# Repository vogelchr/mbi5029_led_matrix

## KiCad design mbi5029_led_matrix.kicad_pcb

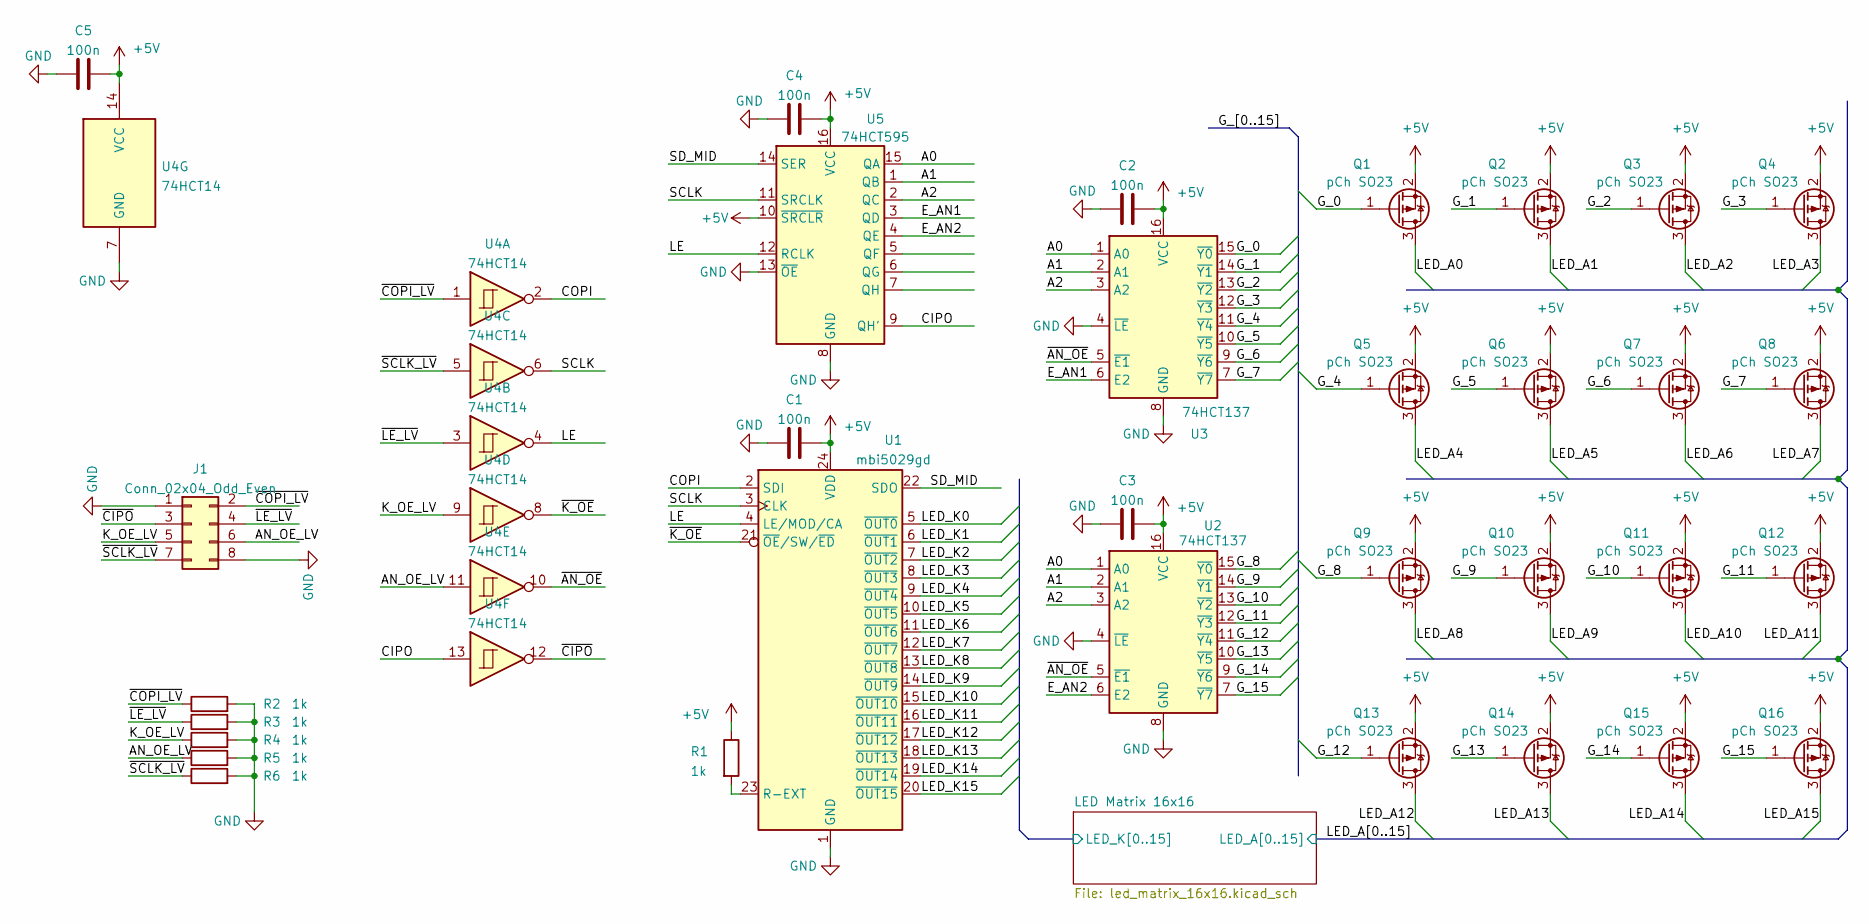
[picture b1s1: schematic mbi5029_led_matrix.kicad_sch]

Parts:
C1, C2, C3, C4, C5: 100n; C_0603_1608Metric
J1: Conn_02x04_Odd_Even; PinHeader_2x04_P2.54mm_Vertical
Q1, Q2, Q3, Q4, Q5, Q6, Q7, Q8, Q9, Q10, Q11, Q12, Q13, Q14, Q15, Q16: pCh SO23; SOT-23
R1, R2, R3, R4, R5, R6: 1k; R_0603_1608Metric
U1: mbi5029gd; SOIC-24W_7.5x15.4mm_P1.27mm
U2, U3: 74HCT137; SOIC-16_3.9x9.9mm_P1.27mm
U4: 74HCT14; SOIC-14_3.9x8.7mm_P1.27mm
U5: 74HCT595; SOIC-16_3.9x9.9mm_P1.27mm

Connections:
+5V: C1.2, C2.2, C3.2, C4.2, C5.2, Q1.2 (S), Q2.2 (S), Q3.2 (S), Q4.2 (S), Q5.2 (S), Q6.2 (S), Q7.2 (S), Q8.2 (S), Q9.2 (S), Q10.2 (S), Q11.2 (S), Q12.2 (S), Q13.2 (S), Q14.2 (S), Q15.2 (S), Q16.2 (S), R1.1, U1.24 (VDD), U2.16 (VCC), U3.16 (VCC), U4.14 (VCC), U5.10 (~SRCLR), U5.16 (VCC)
/A0: U2.1 (A0), U3.1 (A0), U5.15 (QA)
/A1: U2.2 (A1), U3.2 (A1), U5.1 (QB)
/A2: U2.3 (A2), U3.3 (A2), U5.2 (QC)
/AN_OE_LV: J1.6, R5.1, U4.11
/CIPO: U4.13, U5.9 (QH')
/COPI: U1.2 (SDI), U4.2
/E_AN1: U3.6 (E2), U5.3 (QD)
/E_AN2: U2.6 (E2), U5.4 (QE)
/G_0: Q1.1 (G), U3.15 (~Y0)
/G_1: Q2.1 (G), U3.14 (~Y1)
/G_2: Q3.1 (G), U3.13 (~Y2)
/G_3: Q4.1 (G), U3.12 (~Y3)
/G_4: Q5.1 (G), U3.11 (~Y4)
/G_5: Q6.1 (G), U3.10 (~Y5)
/G_6: Q7.1 (G), U3.9 (~Y6)
/G_7: Q8.1 (G), U3.7 (~Y7)
/G_8: Q9.1 (G), U2.15 (~Y0)
/G_9: Q10.1 (G), U2.14 (~Y1)
/G_10: Q11.1 (G), U2.13 (~Y2)
/G_11: Q12.1 (G), U2.12 (~Y3)
/G_12: Q13.1 (G), U2.11 (~Y4)
/G_13: Q14.1 (G), U2.10 (~Y5)
/G_14: Q15.1 (G), U2.9 (~Y6)
/G_15: Q16.1 (G), U2.7 (~Y7)
/K_OE_LV: J1.5, R4.1, U4.9
/LE: U1.4 (LE/MOD/CA), U4.4, U5.12 (RCLK)
/LED Matrix 16x16/LED_K0: U1.5 (~OUT0); also elsewhere on the board
/LED Matrix 16x16/LED_K1: U1.6 (~OUT1); also elsewhere on the board
/LED Matrix 16x16/LED_K2: U1.7 (~OUT2); also elsewhere on the board
/LED Matrix 16x16/LED_K3: U1.8 (~OUT3); also elsewhere on the board
/LED Matrix 16x16/LED_K4: U1.9 (~OUT4); also elsewhere on the board
/LED Matrix 16x16/LED_K5: U1.10 (~OUT5); also elsewhere on the board
/LED Matrix 16x16/LED_K6: U1.11 (~OUT6); also elsewhere on the board
/LED Matrix 16x16/LED_K7: U1.12 (~OUT7); also elsewhere on the board
/LED Matrix 16x16/LED_K8: U1.13 (~OUT8); also elsewhere on the board
/LED Matrix 16x16/LED_K9: U1.14 (~OUT9); also elsewhere on the board
/LED Matrix 16x16/LED_K10: U1.15 (~OUT10); also elsewhere on the board
/LED Matrix 16x16/LED_K11: U1.16 (~OUT11); also elsewhere on the board
/LED Matrix 16x16/LED_K12: U1.17 (~OUT12); also elsewhere on the board
/LED Matrix 16x16/LED_K13: U1.18 (~OUT13); also elsewhere on the board
/LED Matrix 16x16/LED_K14: U1.19 (~OUT14); also elsewhere on the board
/LED Matrix 16x16/LED_K15: U1.20 (~OUT15); also elsewhere on the board
/LED_A0: Q1.3 (D); also elsewhere on the board
/LED_A1: Q2.3 (D); also elsewhere on the board
/LED_A2: Q3.3 (D); also elsewhere on the board
/LED_A3: Q4.3 (D); also elsewhere on the board
/LED_A4: Q5.3 (D); also elsewhere on the board
/LED_A5: Q6.3 (D); also elsewhere on the board
/LED_A6: Q7.3 (D); also elsewhere on the board
/LED_A7: Q8.3 (D); also elsewhere on the board
/LED_A8: Q9.3 (D); also elsewhere on the board
/LED_A9: Q10.3 (D); also elsewhere on the board
/LED_A10: Q11.3 (D); also elsewhere on the board
/LED_A11: Q12.3 (D); also elsewhere on the board
/LED_A12: Q13.3 (D); also elsewhere on the board
/LED_A13: Q14.3 (D); also elsewhere on the board
/LED_A14: Q15.3 (D); also elsewhere on the board
/LED_A15: Q16.3 (D); also elsewhere on the board
/SCLK: U1.3 (CLK), U4.6, U5.11 (SRCLK)
/SD_MID: U1.22 (SDO), U5.14 (SER)
/~AN_OE: U2.5 (~E1), U3.5 (~E1), U4.10
/~CIPO: J1.3, U4.12
/~COPI_LV: J1.2, R2.1, U4.1
/~K_OE: U1.21 (~OE/SW/~ED), U4.8
/~LE_LV: J1.4, R3.1, U4.3
/~SCLK_LV: J1.7, R6.1, U4.5
GND: C1.1, C2.1, C3.1, C4.1, C5.1, J1.1, J1.8, R2.2, R3.2, R4.2, R5.2, R6.2, U1.1 (GND), U2.4 (~LE), U2.8 (GND), U3.4 (~LE), U3.8 (GND), U4.7 (GND), U5.8 (GND), U5.13 (~OE)
unnamed: R1.2, U1.23 (R-EXT)

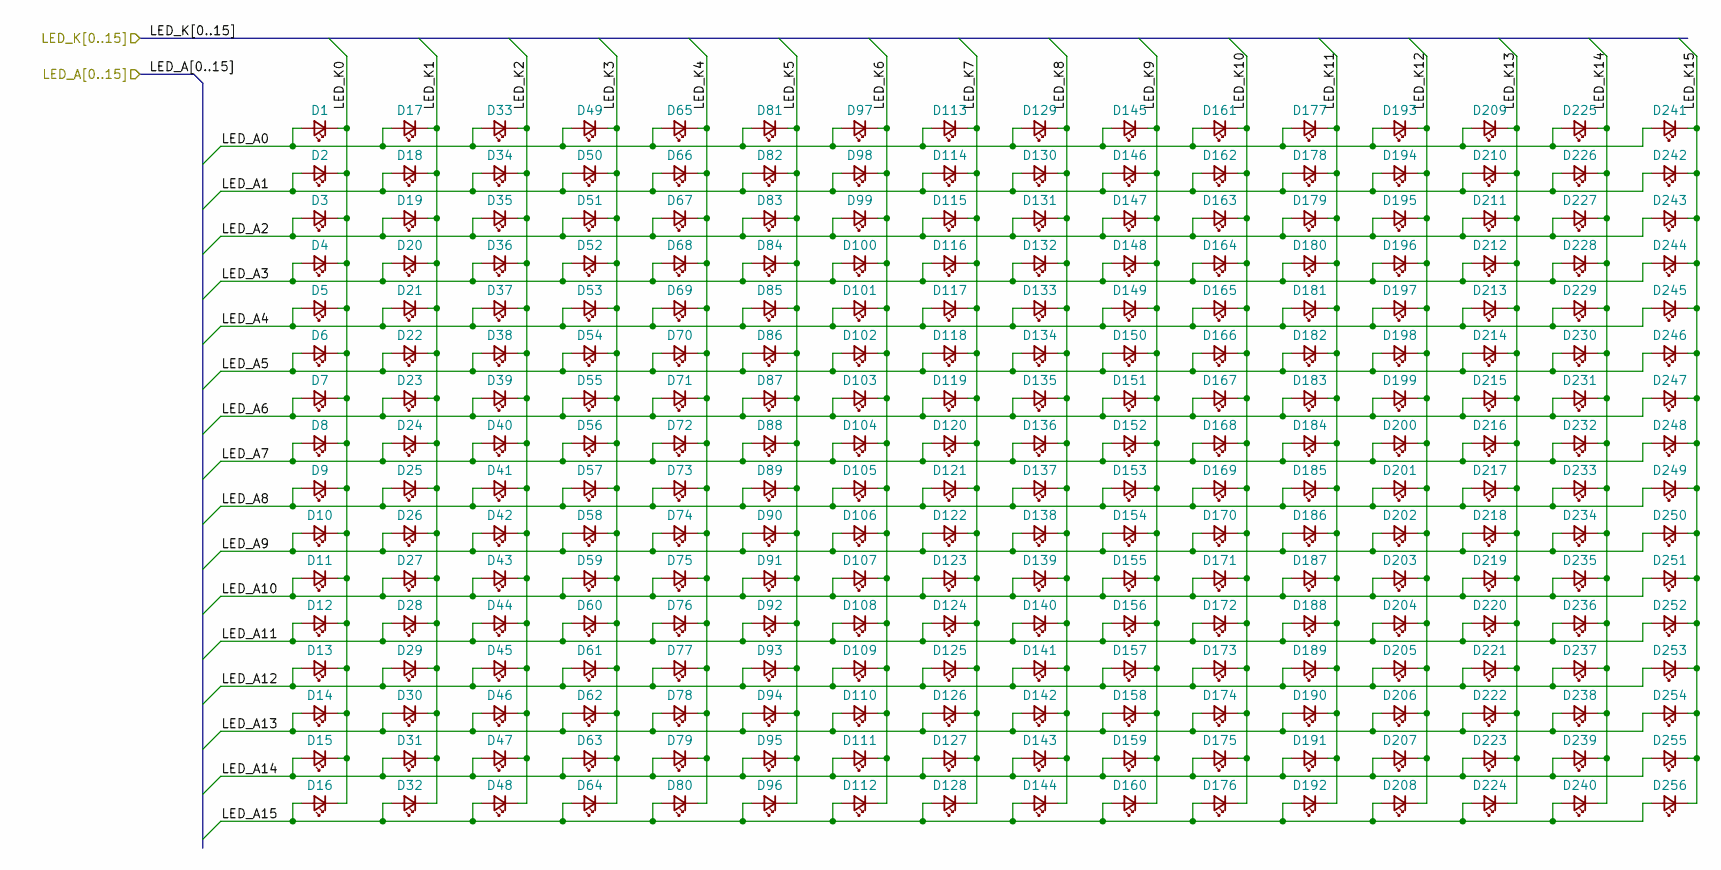
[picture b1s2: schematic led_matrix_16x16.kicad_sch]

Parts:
D1, D2, D3, D4, D5, D6, D7, D8, D9, D10, D11, D12, D13, D14, D15, D16, D17, D18, D19, D20, D21, D22, D23, D24, D25, D26, D27, D28, D29, D30, D31, D32, D33, D34, D35, D36, D37, D38, D39, D40, D41, D42, D43, D44, D45, D46, D47, D48, D49, D50, D51, D52, D53, D54, D55, D56, D57, D58, D59, D60, D61, D62, D63, D64, D65, D66, D67, D68, D69, D70, D71, D72, D73, D74, D75, D76, D77, D78, D79, D80, D81, D82, D83, D84, D85, D86, D87, D88, D89, D90, D91, D92, D93, D94, D95, D96, D97, D98, D99, D100, D101, D102, D103, D104, D105, D106, D107, D108, D109, D110, D111, D112, D113, D114, D115, D116, D117, D118, D119, D120, D121, D122, D123, D124, D125, D126, D127, D128, D129, D130, D131, D132, D133, D134, D135, D136, D137, D138, D139, D140, D141, D142, D143, D144, D145, D146, D147, D148, D149, D150, D151, D152, D153, D154, D155, D156, D157, D158, D159, D160, D161, D162, D163, D164, D165, D166, D167, D168, D169, D170, D171, D172, D173, D174, D175, D176, D177, D178, D179, D180, D181, D182, D183, D184, D185, D186, D187, D188, D189, D190, D191, D192, D193, D194, D195, D196, D197, D198, D199, D200, D201, D202, D203, D204, D205, D206, D207, D208, D209, D210, D211, D212, D213, D214, D215, D216, D217, D218, D219, D220, D221, D222, D223, D224, D225, D226, D227, D228, D229, D230, D231, D232, D233, D234, D235, D236, D237, D238, D239, D240, D241, D242, D243, D244, D245, D246, D247, D248, D249, D250, D251, D252, D253, D254, D255, D256: LED_Small; LED_0603_1608Metric

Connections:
/LED Matrix 16x16/LED_K0: D1.1 (K), D2.1 (K), D3.1 (K), D4.1 (K), D5.1 (K), D6.1 (K), D7.1 (K), D8.1 (K), D9.1 (K), D10.1 (K), D11.1 (K), D12.1 (K), D13.1 (K), D14.1 (K), D15.1 (K), D16.1 (K); also elsewhere on the board
/LED Matrix 16x16/LED_K1: D17.1 (K), D18.1 (K), D19.1 (K), D20.1 (K), D21.1 (K), D22.1 (K), D23.1 (K), D24.1 (K), D25.1 (K), D26.1 (K), D27.1 (K), D28.1 (K), D29.1 (K), D30.1 (K), D31.1 (K), D32.1 (K); also elsewhere on the board
/LED Matrix 16x16/LED_K2: D33.1 (K), D34.1 (K), D35.1 (K), D36.1 (K), D37.1 (K), D38.1 (K), D39.1 (K), D40.1 (K), D41.1 (K), D42.1 (K), D43.1 (K), D44.1 (K), D45.1 (K), D46.1 (K), D47.1 (K), D48.1 (K); also elsewhere on the board
/LED Matrix 16x16/LED_K3: D49.1 (K), D50.1 (K), D51.1 (K), D52.1 (K), D53.1 (K), D54.1 (K), D55.1 (K), D56.1 (K), D57.1 (K), D58.1 (K), D59.1 (K), D60.1 (K), D61.1 (K), D62.1 (K), D63.1 (K), D64.1 (K); also elsewhere on the board
/LED Matrix 16x16/LED_K4: D65.1 (K), D66.1 (K), D67.1 (K), D68.1 (K), D69.1 (K), D70.1 (K), D71.1 (K), D72.1 (K), D73.1 (K), D74.1 (K), D75.1 (K), D76.1 (K), D77.1 (K), D78.1 (K), D79.1 (K), D80.1 (K); also elsewhere on the board
/LED Matrix 16x16/LED_K5: D81.1 (K), D82.1 (K), D83.1 (K), D84.1 (K), D85.1 (K), D86.1 (K), D87.1 (K), D88.1 (K), D89.1 (K), D90.1 (K), D91.1 (K), D92.1 (K), D93.1 (K), D94.1 (K), D95.1 (K), D96.1 (K); also elsewhere on the board
/LED Matrix 16x16/LED_K6: D97.1 (K), D98.1 (K), D99.1 (K), D100.1 (K), D101.1 (K), D102.1 (K), D103.1 (K), D104.1 (K), D105.1 (K), D106.1 (K), D107.1 (K), D108.1 (K), D109.1 (K), D110.1 (K), D111.1 (K), D112.1 (K); also elsewhere on the board
/LED Matrix 16x16/LED_K7: D113.1 (K), D114.1 (K), D115.1 (K), D116.1 (K), D117.1 (K), D118.1 (K), D119.1 (K), D120.1 (K), D121.1 (K), D122.1 (K), D123.1 (K), D124.1 (K), D125.1 (K), D126.1 (K), D127.1 (K), D128.1 (K); also elsewhere on the board
/LED Matrix 16x16/LED_K8: D129.1 (K), D130.1 (K), D131.1 (K), D132.1 (K), D133.1 (K), D134.1 (K), D135.1 (K), D136.1 (K), D137.1 (K), D138.1 (K), D139.1 (K), D140.1 (K), D141.1 (K), D142.1 (K), D143.1 (K), D144.1 (K); also elsewhere on the board
/LED Matrix 16x16/LED_K9: D145.1 (K), D146.1 (K), D147.1 (K), D148.1 (K), D149.1 (K), D150.1 (K), D151.1 (K), D152.1 (K), D153.1 (K), D154.1 (K), D155.1 (K), D156.1 (K), D157.1 (K), D158.1 (K), D159.1 (K), D160.1 (K); also elsewhere on the board
/LED Matrix 16x16/LED_K10: D161.1 (K), D162.1 (K), D163.1 (K), D164.1 (K), D165.1 (K), D166.1 (K), D167.1 (K), D168.1 (K), D169.1 (K), D170.1 (K), D171.1 (K), D172.1 (K), D173.1 (K), D174.1 (K), D175.1 (K), D176.1 (K); also elsewhere on the board
/LED Matrix 16x16/LED_K11: D177.1 (K), D178.1 (K), D179.1 (K), D180.1 (K), D181.1 (K), D182.1 (K), D183.1 (K), D184.1 (K), D185.1 (K), D186.1 (K), D187.1 (K), D188.1 (K), D189.1 (K), D190.1 (K), D191.1 (K), D192.1 (K); also elsewhere on the board
/LED Matrix 16x16/LED_K12: D193.1 (K), D194.1 (K), D195.1 (K), D196.1 (K), D197.1 (K), D198.1 (K), D199.1 (K), D200.1 (K), D201.1 (K), D202.1 (K), D203.1 (K), D204.1 (K), D205.1 (K), D206.1 (K), D207.1 (K), D208.1 (K); also elsewhere on the board
/LED Matrix 16x16/LED_K13: D209.1 (K), D210.1 (K), D211.1 (K), D212.1 (K), D213.1 (K), D214.1 (K), D215.1 (K), D216.1 (K), D217.1 (K), D218.1 (K), D219.1 (K), D220.1 (K), D221.1 (K), D222.1 (K), D223.1 (K), D224.1 (K); also elsewhere on the board
/LED Matrix 16x16/LED_K14: D225.1 (K), D226.1 (K), D227.1 (K), D228.1 (K), D229.1 (K), D230.1 (K), D231.1 (K), D232.1 (K), D233.1 (K), D234.1 (K), D235.1 (K), D236.1 (K), D237.1 (K), D238.1 (K), D239.1 (K), D240.1 (K); also elsewhere on the board
/LED Matrix 16x16/LED_K15: D241.1 (K), D242.1 (K), D243.1 (K), D244.1 (K), D245.1 (K), D246.1 (K), D247.1 (K), D248.1 (K), D249.1 (K), D250.1 (K), D251.1 (K), D252.1 (K), D253.1 (K), D254.1 (K), D255.1 (K), D256.1 (K); also elsewhere on the board
/LED_A0: D1.2 (A), D17.2 (A), D33.2 (A), D49.2 (A), D65.2 (A), D81.2 (A), D97.2 (A), D113.2 (A), D129.2 (A), D145.2 (A), D161.2 (A), D177.2 (A), D193.2 (A), D209.2 (A), D225.2 (A), D241.2 (A); also elsewhere on the board
/LED_A1: D2.2 (A), D18.2 (A), D34.2 (A), D50.2 (A), D66.2 (A), D82.2 (A), D98.2 (A), D114.2 (A), D130.2 (A), D146.2 (A), D162.2 (A), D178.2 (A), D194.2 (A), D210.2 (A), D226.2 (A), D242.2 (A); also elsewhere on the board
/LED_A2: D3.2 (A), D19.2 (A), D35.2 (A), D51.2 (A), D67.2 (A), D83.2 (A), D99.2 (A), D115.2 (A), D131.2 (A), D147.2 (A), D163.2 (A), D179.2 (A), D195.2 (A), D211.2 (A), D227.2 (A), D243.2 (A); also elsewhere on the board
/LED_A3: D4.2 (A), D20.2 (A), D36.2 (A), D52.2 (A), D68.2 (A), D84.2 (A), D100.2 (A), D116.2 (A), D132.2 (A), D148.2 (A), D164.2 (A), D180.2 (A), D196.2 (A), D212.2 (A), D228.2 (A), D244.2 (A); also elsewhere on the board
/LED_A4: D5.2 (A), D21.2 (A), D37.2 (A), D53.2 (A), D69.2 (A), D85.2 (A), D101.2 (A), D117.2 (A), D133.2 (A), D149.2 (A), D165.2 (A), D181.2 (A), D197.2 (A), D213.2 (A), D229.2 (A), D245.2 (A); also elsewhere on the board
/LED_A5: D6.2 (A), D22.2 (A), D38.2 (A), D54.2 (A), D70.2 (A), D86.2 (A), D102.2 (A), D118.2 (A), D134.2 (A), D150.2 (A), D166.2 (A), D182.2 (A), D198.2 (A), D214.2 (A), D230.2 (A), D246.2 (A); also elsewhere on the board
/LED_A6: D7.2 (A), D23.2 (A), D39.2 (A), D55.2 (A), D71.2 (A), D87.2 (A), D103.2 (A), D119.2 (A), D135.2 (A), D151.2 (A), D167.2 (A), D183.2 (A), D199.2 (A), D215.2 (A), D231.2 (A), D247.2 (A); also elsewhere on the board
/LED_A7: D8.2 (A), D24.2 (A), D40.2 (A), D56.2 (A), D72.2 (A), D88.2 (A), D104.2 (A), D120.2 (A), D136.2 (A), D152.2 (A), D168.2 (A), D184.2 (A), D200.2 (A), D216.2 (A), D232.2 (A), D248.2 (A); also elsewhere on the board
/LED_A8: D9.2 (A), D25.2 (A), D41.2 (A), D57.2 (A), D73.2 (A), D89.2 (A), D105.2 (A), D121.2 (A), D137.2 (A), D153.2 (A), D169.2 (A), D185.2 (A), D201.2 (A), D217.2 (A), D233.2 (A), D249.2 (A); also elsewhere on the board
/LED_A9: D10.2 (A), D26.2 (A), D42.2 (A), D58.2 (A), D74.2 (A), D90.2 (A), D106.2 (A), D122.2 (A), D138.2 (A), D154.2 (A), D170.2 (A), D186.2 (A), D202.2 (A), D218.2 (A), D234.2 (A), D250.2 (A); also elsewhere on the board
/LED_A10: D11.2 (A), D27.2 (A), D43.2 (A), D59.2 (A), D75.2 (A), D91.2 (A), D107.2 (A), D123.2 (A), D139.2 (A), D155.2 (A), D171.2 (A), D187.2 (A), D203.2 (A), D219.2 (A), D235.2 (A), D251.2 (A); also elsewhere on the board
/LED_A11: D12.2 (A), D28.2 (A), D44.2 (A), D60.2 (A), D76.2 (A), D92.2 (A), D108.2 (A), D124.2 (A), D140.2 (A), D156.2 (A), D172.2 (A), D188.2 (A), D204.2 (A), D220.2 (A), D236.2 (A), D252.2 (A); also elsewhere on the board
/LED_A12: D13.2 (A), D29.2 (A), D45.2 (A), D61.2 (A), D77.2 (A), D93.2 (A), D109.2 (A), D125.2 (A), D141.2 (A), D157.2 (A), D173.2 (A), D189.2 (A), D205.2 (A), D221.2 (A), D237.2 (A), D253.2 (A); also elsewhere on the board
/LED_A13: D14.2 (A), D30.2 (A), D46.2 (A), D62.2 (A), D78.2 (A), D94.2 (A), D110.2 (A), D126.2 (A), D142.2 (A), D158.2 (A), D174.2 (A), D190.2 (A), D206.2 (A), D222.2 (A), D238.2 (A), D254.2 (A); also elsewhere on the board
/LED_A14: D15.2 (A), D31.2 (A), D47.2 (A), D63.2 (A), D79.2 (A), D95.2 (A), D111.2 (A), D127.2 (A), D143.2 (A), D159.2 (A), D175.2 (A), D191.2 (A), D207.2 (A), D223.2 (A), D239.2 (A), D255.2 (A); also elsewhere on the board
/LED_A15: D16.2 (A), D32.2 (A), D48.2 (A), D64.2 (A), D80.2 (A), D96.2 (A), D112.2 (A), D128.2 (A), D144.2 (A), D160.2 (A), D176.2 (A), D192.2 (A), D208.2 (A), D224.2 (A), D240.2 (A), D256.2 (A); also elsewhere on the board

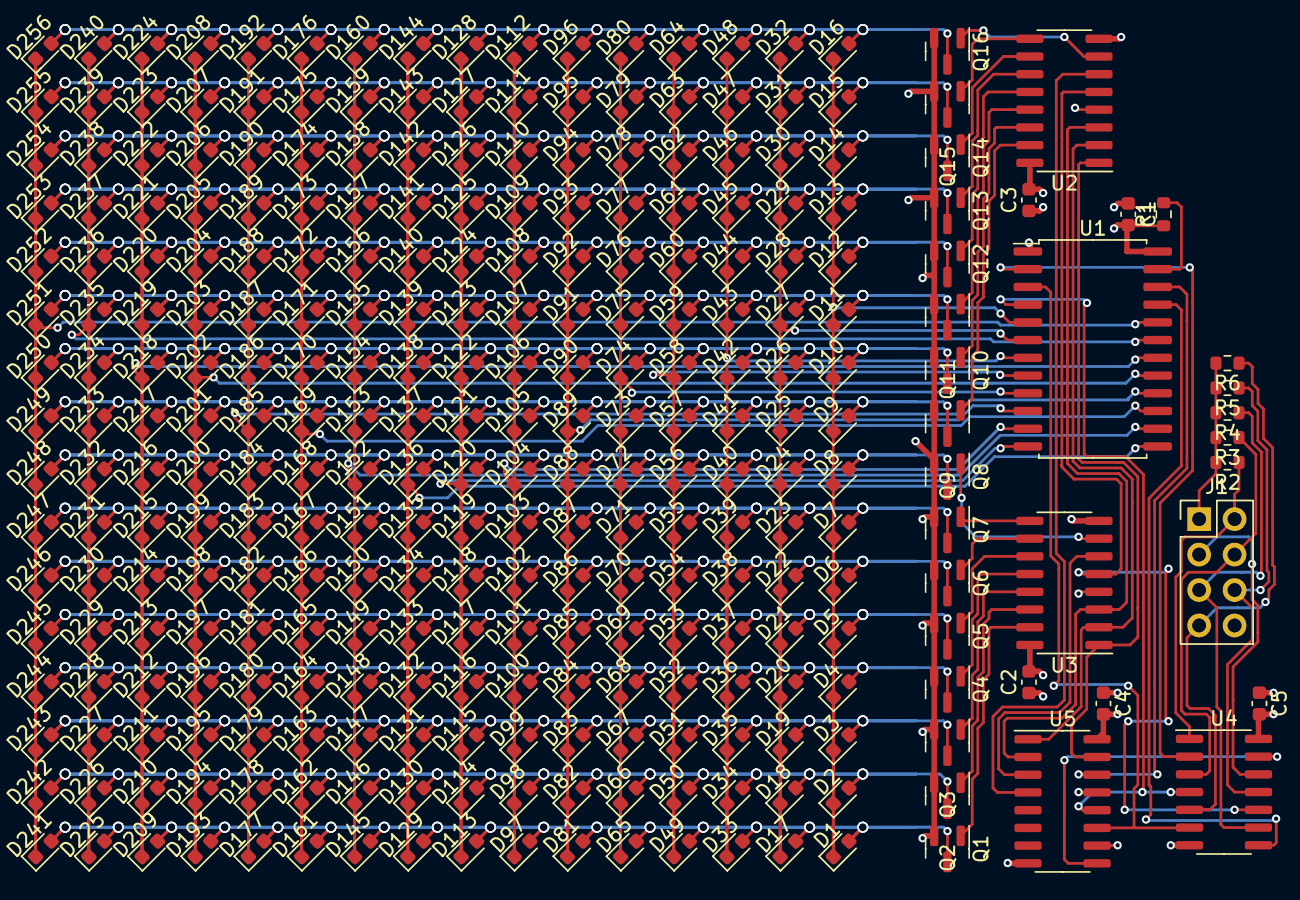
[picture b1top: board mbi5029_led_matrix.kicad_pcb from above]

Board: 4 copper layers, 289 parts (0 on the bottom side), 69 nets.

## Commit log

2021-09-16 initial
2021-09-16 work
2021-09-17 more work!
2021-09-19 more work
